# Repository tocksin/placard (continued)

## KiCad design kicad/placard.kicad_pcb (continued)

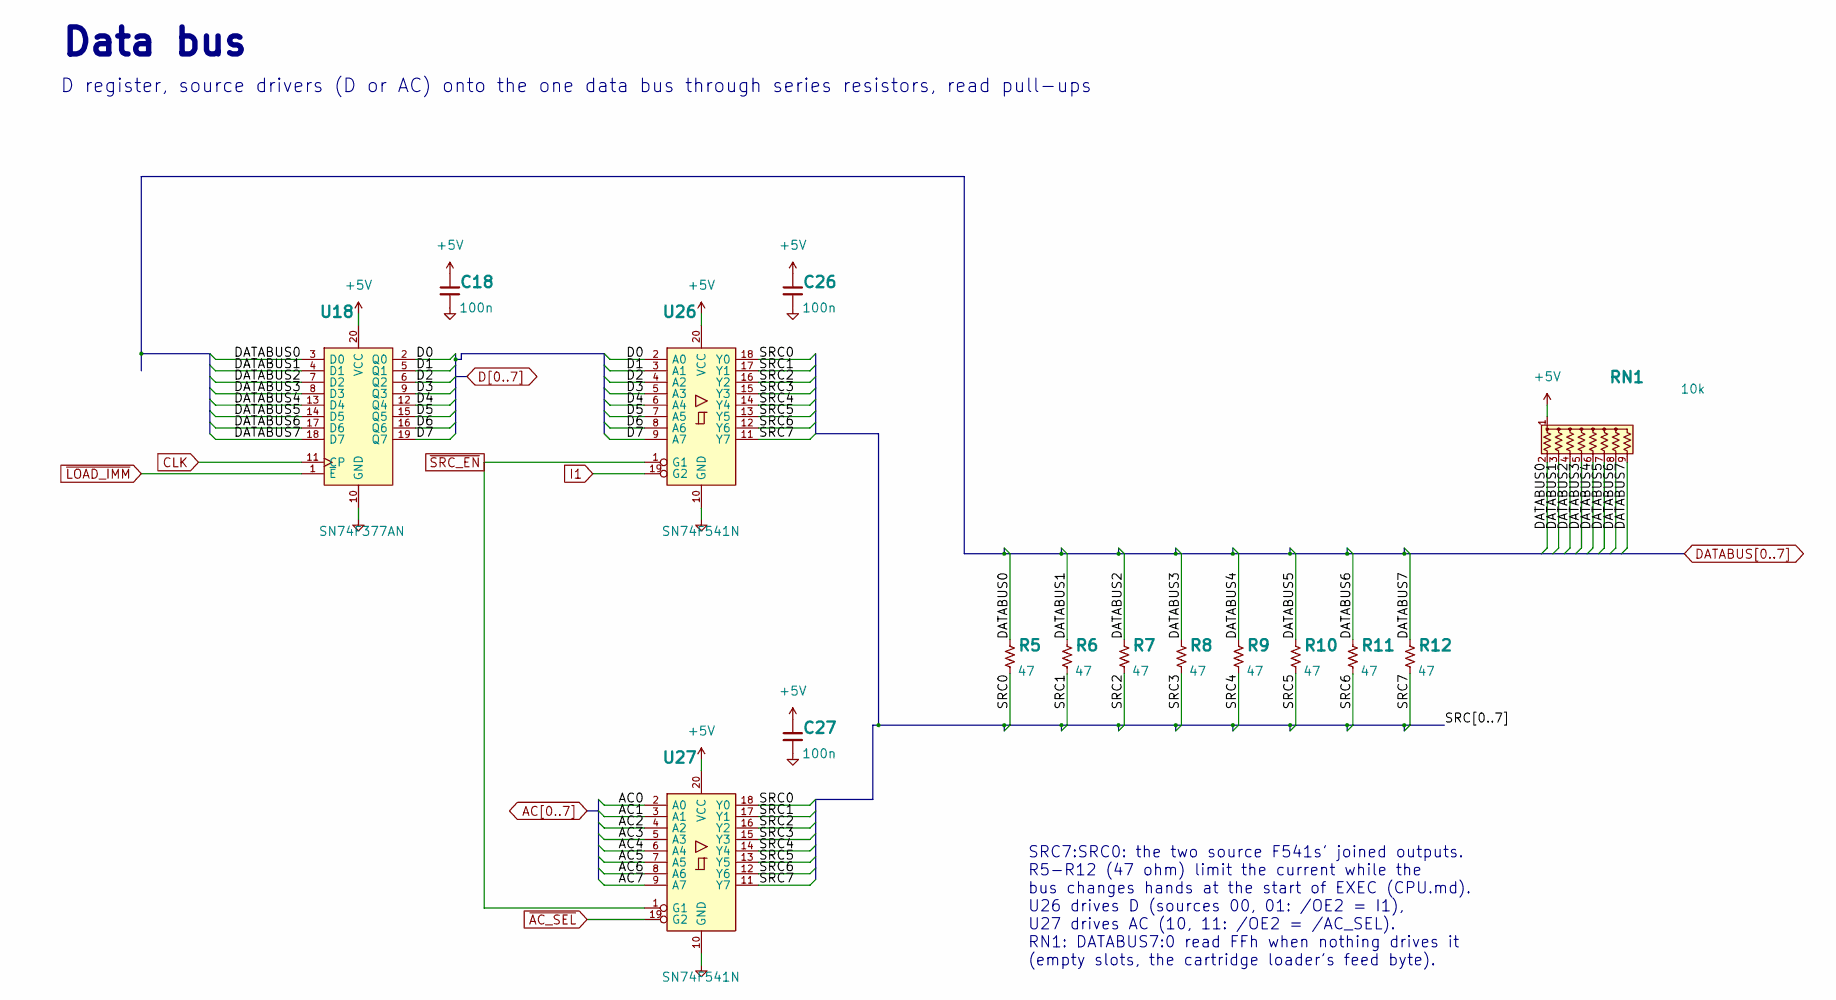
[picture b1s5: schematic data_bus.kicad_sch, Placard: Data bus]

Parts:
C18, C26, C27: 100n; C_Disc_D5.0mm_W2.5mm_P5.00mm; MPN FG28X7R1H104KNT00
R5, R6, R7, R8, R9, R10, R11, R12: 47; R_Axial_DIN0207_L6.3mm_D2.5mm_P10.16mm_Horizontal_Value; MPN MFR-25FBF52-47R
RN1: 10k; R_Array_SIP9; MPN 4609X-101-103LF
U18: SN74F377AN; DIP-20_W7.62mm_Socket_Puller; MPN SN74F377AN
U26, U27: SN74F541N; DIP-20_W7.62mm_Socket_Puller; MPN SN74F541N

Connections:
+5V: C18.1, C26.1, C27.1, RN1.1 (common), U18.20 (VCC), U26.20 (VCC), U27.20 (VCC); also elsewhere on the board
/Data bus/SRC0: R5.2, U26.18 (Y0), U27.18 (Y0)
/Data bus/SRC1: R6.2, U26.17 (Y1), U27.17 (Y1)
/Data bus/SRC2: R7.2, U26.16 (Y2), U27.16 (Y2)
/Data bus/SRC3: R8.2, U26.15 (Y3), U27.15 (Y3)
/Data bus/SRC4: R9.2, U26.14 (Y4), U27.14 (Y4)
/Data bus/SRC5: R10.2, U26.13 (Y5), U27.13 (Y5)
/Data bus/SRC6: R11.2, U26.12 (Y6), U27.12 (Y6)
/Data bus/SRC7: R12.2, U26.11 (Y7), U27.11 (Y7)
AC0: U27.2 (A0); also elsewhere on the board
AC1: U27.3 (A1); also elsewhere on the board
AC2: U27.4 (A2); also elsewhere on the board
AC3: U27.5 (A3); also elsewhere on the board
AC4: U27.6 (A4); also elsewhere on the board
AC5: U27.7 (A5); also elsewhere on the board
AC6: U27.8 (A6); also elsewhere on the board
AC7: U27.9 (A7); also elsewhere on the board
CLK: U18.11 (CP); also elsewhere on the board
D0: U18.2 (Q0), U26.2 (A0); also elsewhere on the board
D1: U18.5 (Q1), U26.3 (A1); also elsewhere on the board
D2: U18.6 (Q2), U26.4 (A2); also elsewhere on the board
D3: U18.9 (Q3), U26.5 (A3); also elsewhere on the board
D4: U18.12 (Q4), U26.6 (A4); also elsewhere on the board
D5: U18.15 (Q5), U26.7 (A5); also elsewhere on the board
D6: U18.16 (Q6), U26.8 (A6); also elsewhere on the board
D7: U18.19 (Q7), U26.9 (A7); also elsewhere on the board
DATABUS0: R5.1, RN1.2 (R1), U18.3 (D0); also elsewhere on the board
DATABUS1: R6.1, RN1.3 (R2), U18.4 (D1); also elsewhere on the board
DATABUS2: R7.1, RN1.4 (R3), U18.7 (D2); also elsewhere on the board
DATABUS3: R8.1, RN1.5 (R4), U18.8 (D3); also elsewhere on the board
DATABUS4: R9.1, RN1.6 (R5), U18.13 (D4); also elsewhere on the board
DATABUS5: R10.1, RN1.7 (R6), U18.14 (D5); also elsewhere on the board
DATABUS6: R11.1, RN1.8 (R7), U18.17 (D6); also elsewhere on the board
DATABUS7: R12.1, RN1.9 (R8), U18.18 (D7); also elsewhere on the board
GND: C18.2, C26.2, C27.2, U18.10 (GND), U26.10 (GND), U27.10 (GND); also elsewhere on the board
I1: U26.19 (G2); also elsewhere on the board
~AC_SEL: U27.19 (G2); also elsewhere on the board
~LOAD_IMM: U18.1 (~E); also elsewhere on the board
~SRC_EN: U26.1 (G1), U27.1 (G1); also elsewhere on the board

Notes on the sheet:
SRC7:SRC0: the two source F541s' joined outputs.
RN1: DATABUS7:0 read FFh when nothing drives it
U27 drives AC (10, 11: /OE2 = /AC_SEL).
R5-R12 (47 ohm) limit the current while the
Data bus
D register, source drivers (D or AC) onto the one data bus through series resistors, read pull-ups
bus changes hands at the start of EXEC (CPU.md).
U26 drives D (sources 00, 01: /OE2 = I1),
(empty slots, the cartridge loader's feed byte).

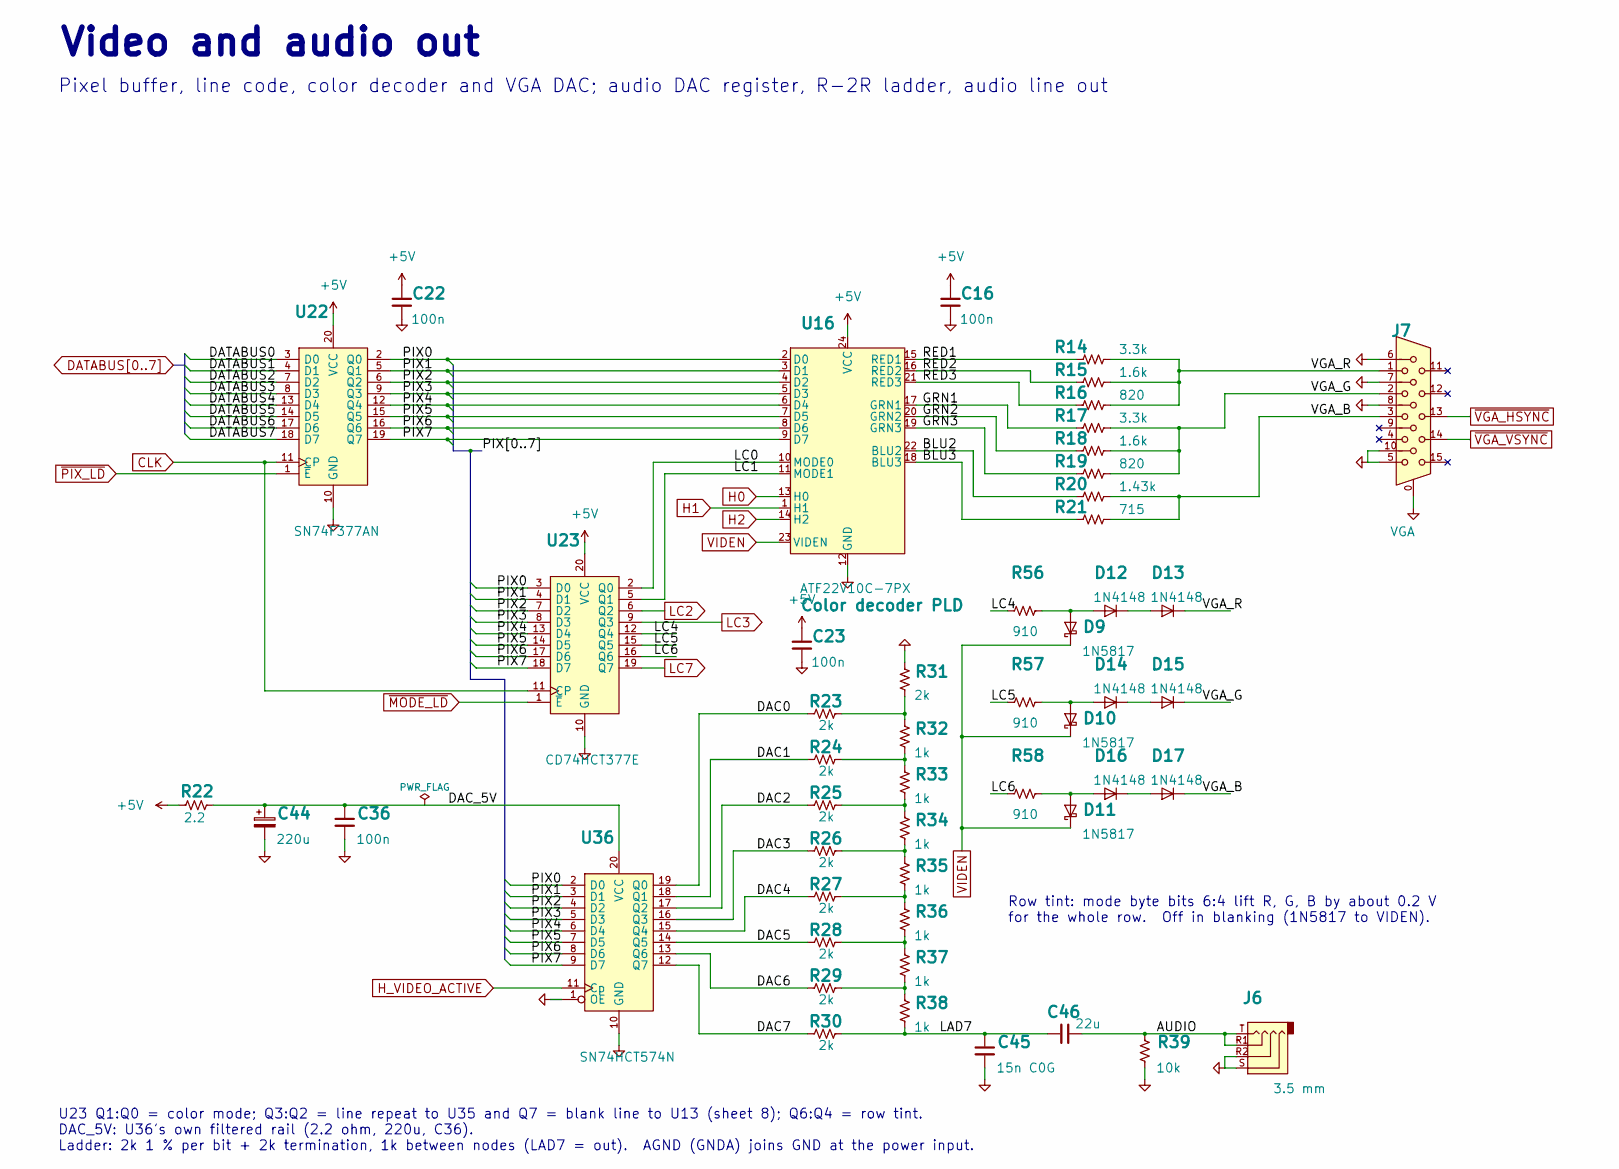
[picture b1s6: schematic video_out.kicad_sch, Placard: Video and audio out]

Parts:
C16, C22, C23, C36: 100n; C_Disc_D5.0mm_W2.5mm_P5.00mm; MPN FG28X7R1H104KNT00
C44: 220u; CP_Radial_D6.3mm_P2.50mm; MPN 25YXJ220M6.3X11
C45: 15n C0G; C_Disc_D5.0mm_W2.5mm_P5.00mm; MPN FG24C0G1H153JNT06
C46: 22u; C_Disc_D5.0mm_W2.5mm_P5.00mm; MPN FG22X7R1E226MRT06
D9, D10, D11: 1N5817; D_DO-41_SOD81_P7.62mm_Horizontal_Pad1.6; MPN 1N5817-TP
D12, D13, D14, D15, D16, D17: 1N4148; D_DO-35_SOD27_P7.62mm_Horizontal; MPN 1N4148-TAP
J6: 3.5 mm; Jack_3.5mm_Tensility_54-00174_Horizontal; MPN 54-00174
J7: VGA; DSUB-15-HD_Female_Horizontal_P2.29x1.98mm_EdgePinOffset3.03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; MPN A-HDF 15 A-KG/T
R14, R17: 3.3k; R_Axial_DIN0207_L6.3mm_D2.5mm_P10.16mm_Horizontal_Value; MPN MFR-25FBF52-3K3
R15, R18: 1.6k; R_Axial_DIN0207_L6.3mm_D2.5mm_P10.16mm_Horizontal_Value; MPN MFR-25FBF52-1K6
R16, R19: 820; R_Axial_DIN0207_L6.3mm_D2.5mm_P10.16mm_Horizontal_Value; MPN MFR-25FBF52-820R
R20: 1.43k; R_Axial_DIN0207_L6.3mm_D2.5mm_P10.16mm_Horizontal_Value; MPN MFR-25FBF52-1K43
R21: 715; R_Axial_DIN0207_L6.3mm_D2.5mm_P10.16mm_Horizontal_Value; MPN MFR-25FBF52-715R
R22: 2.2; R_Axial_DIN0207_L6.3mm_D2.5mm_P10.16mm_Horizontal_Value; MPN MFR-25FBF52-2R2
R23, R24, R25, R26, R27, R28, R29, R30, R31: 2k; R_Axial_DIN0207_L6.3mm_D2.5mm_P10.16mm_Horizontal_Value; MPN MFR-25FBF52-2K
R32, R33, R34, R35, R36, R37, R38: 1k; R_Axial_DIN0207_L6.3mm_D2.5mm_P10.16mm_Horizontal_Value; MPN MFR-25FBF52-1K
R39: 10k; R_Axial_DIN0207_L6.3mm_D2.5mm_P10.16mm_Horizontal_Value; MPN MFR-25FBF52-10K
R56, R57, R58: 910; R_Axial_DIN0207_L6.3mm_D2.5mm_P10.16mm_Horizontal_Value; MPN MFR-25FBF52-910R
U16: ATF22V10C-7PX; DIP-24_W7.62mm_Socket_Puller; MPN ATF22V10C-7PX
U22: SN74F377AN; DIP-20_W7.62mm_Socket_Puller; MPN SN74F377AN
U23: CD74HCT377E; DIP-20_W7.62mm_Socket_Puller; MPN CD74HCT377E
U36: SN74HCT574N; DIP-20_W7.62mm_Socket_Puller; MPN SN74HCT574N

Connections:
+5V: C16.1, C22.1, C23.1, R22.1, U16.24 (VCC), U22.20 (VCC), U23.20 (VCC); also elsewhere on the board
/Video and audio out/AUDIO: C46.2, J6.R1, J6.T, R39.1
/Video and audio out/BLU2: R20.1, U16.22 (BLU2)
/Video and audio out/BLU3: R21.1, U16.18 (BLU3)
/Video and audio out/DAC0: R23.1, U36.19 (Q0)
/Video and audio out/DAC1: R24.1, U36.18 (Q1)
/Video and audio out/DAC2: R25.1, U36.17 (Q2)
/Video and audio out/DAC3: R26.1, U36.16 (Q3)
/Video and audio out/DAC4: R27.1, U36.15 (Q4)
/Video and audio out/DAC5: R28.1, U36.14 (Q5)
/Video and audio out/DAC6: R29.1, U36.13 (Q6)
/Video and audio out/DAC7: R30.1, U36.12 (Q7)
/Video and audio out/DAC_5V: C36.1, C44.1, R22.2, U36.20 (VCC)
/Video and audio out/GRN1: R17.1, U16.17 (GRN1)
/Video and audio out/GRN2: R18.1, U16.20 (GRN2)
/Video and audio out/GRN3: R19.1, U16.19 (GRN3)
/Video and audio out/LAD7: C45.1, C46.1, R30.2, R38.2
/Video and audio out/LC0: U16.10 (MODE0), U23.2 (Q0)
/Video and audio out/LC1: U16.11 (MODE1), U23.5 (Q1)
/Video and audio out/LC4: R56.1, U23.12 (Q4)
/Video and audio out/LC5: R57.1, U23.15 (Q5)
/Video and audio out/LC6: R58.1, U23.16 (Q6)
/Video and audio out/PIX0: U16.2 (D0), U22.2 (Q0), U23.3 (D0), U36.2 (D0)
/Video and audio out/PIX1: U16.3 (D1), U22.5 (Q1), U23.4 (D1), U36.3 (D1)
/Video and audio out/PIX2: U16.4 (D2), U22.6 (Q2), U23.7 (D2), U36.4 (D2)
/Video and audio out/PIX3: U16.5 (D3), U22.9 (Q3), U23.8 (D3), U36.5 (D3)
/Video and audio out/PIX4: U16.6 (D4), U22.12 (Q4), U23.13 (D4), U36.6 (D4)
/Video and audio out/PIX5: U16.7 (D5), U22.15 (Q5), U23.14 (D5), U36.7 (D5)
/Video and audio out/PIX6: U16.8 (D6), U22.16 (Q6), U23.17 (D6), U36.8 (D6)
/Video and audio out/PIX7: U16.9 (D7), U22.19 (Q7), U23.18 (D7), U36.9 (D7)
/Video and audio out/RED1: R14.1, U16.15 (RED1)
/Video and audio out/RED2: R15.1, U16.16 (RED2)
/Video and audio out/RED3: R16.1, U16.21 (RED3)
/Video and audio out/VGA_B: D17.1 (K), J7.3, R20.2, R21.2
/Video and audio out/VGA_G: D15.1 (K), J7.2, R17.2, R18.2, R19.2
/Video and audio out/VGA_R: D13.1 (K), J7.1, R14.2, R15.2, R16.2
CLK: U22.11 (CP), U23.11 (CP); also elsewhere on the board
DATABUS0: U22.3 (D0); also elsewhere on the board
DATABUS1: U22.4 (D1); also elsewhere on the board
DATABUS2: U22.7 (D2); also elsewhere on the board
DATABUS3: U22.8 (D3); also elsewhere on the board
DATABUS4: U22.13 (D4); also elsewhere on the board
DATABUS5: U22.14 (D5); also elsewhere on the board
DATABUS6: U22.17 (D6); also elsewhere on the board
DATABUS7: U22.18 (D7); also elsewhere on the board
GND: C16.2, C22.2, C23.2, J7.0, J7.5, J7.6, J7.7, J7.8, J7.10, U16.12 (GND), U22.10 (GND), U23.10 (GND); also elsewhere on the board
GNDA: C36.2, C44.2, C45.2, J6.R2, J6.S, R31.1, R39.2, U36.1 (OE), U36.10 (GND); also elsewhere on the board
H0: U16.13 (H0); also elsewhere on the board
H1: U16.1 (H1); also elsewhere on the board
H2: U16.14 (H2); also elsewhere on the board
H_VIDEO_ACTIVE: U36.11 (Cp); also elsewhere on the board
LC2: U23.6 (Q2); also elsewhere on the board
LC3: U23.9 (Q3); also elsewhere on the board
LC7: U23.19 (Q7); also elsewhere on the board
unnamed: D10.2 (A), D14.2 (A), R57.2
unnamed: D11.2 (A), D16.2 (A), R58.2
unnamed: D9.2 (A), D12.2 (A), R56.2
unnamed: D12.1 (K), D13.2 (A)
unnamed: D14.1 (K), D15.2 (A)
unnamed: D16.1 (K), D17.2 (A)
unnamed: R23.2, R31.2, R32.1
unnamed: R24.2, R32.2, R33.1
unnamed: R25.2, R33.2, R34.1
unnamed: R26.2, R34.2, R35.1
unnamed: R27.2, R35.2, R36.1
unnamed: R28.2, R36.2, R37.1
unnamed: R29.2, R37.2, R38.1
VIDEN: D9.1 (K), D10.1 (K), D11.1 (K), U16.23 (VIDEN); also elsewhere on the board
~MODE_LD: U23.1 (~E); also elsewhere on the board
~PIX_LD: U22.1 (~E); also elsewhere on the board
~VGA_HSYNC: J7.13; also elsewhere on the board
~VGA_VSYNC: J7.14; also elsewhere on the board

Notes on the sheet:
Pixel buffer, line code, color decoder and VGA DAC; audio DAC register, R-2R ladder, audio line out
Video and audio out
U23 Q1:Q0 = color mode; Q3:Q2 = line repeat to U35 and Q7 = blank line to U13 (sheet 8); Q6:Q4 = row tint.
Row tint: mode byte bits 6:4 lift R, G, B by about 0.2 V
DAC_5V: U36's own filtered rail (2.2 ohm, 220u, C36).
for the whole row. Off in blanking (1N5817 to VIDEN).
Ladder: 2k 1 % per bit + 2k termination, 1k between nodes (LAD7 = out). AGND (GNDA) joins GND at the power input.

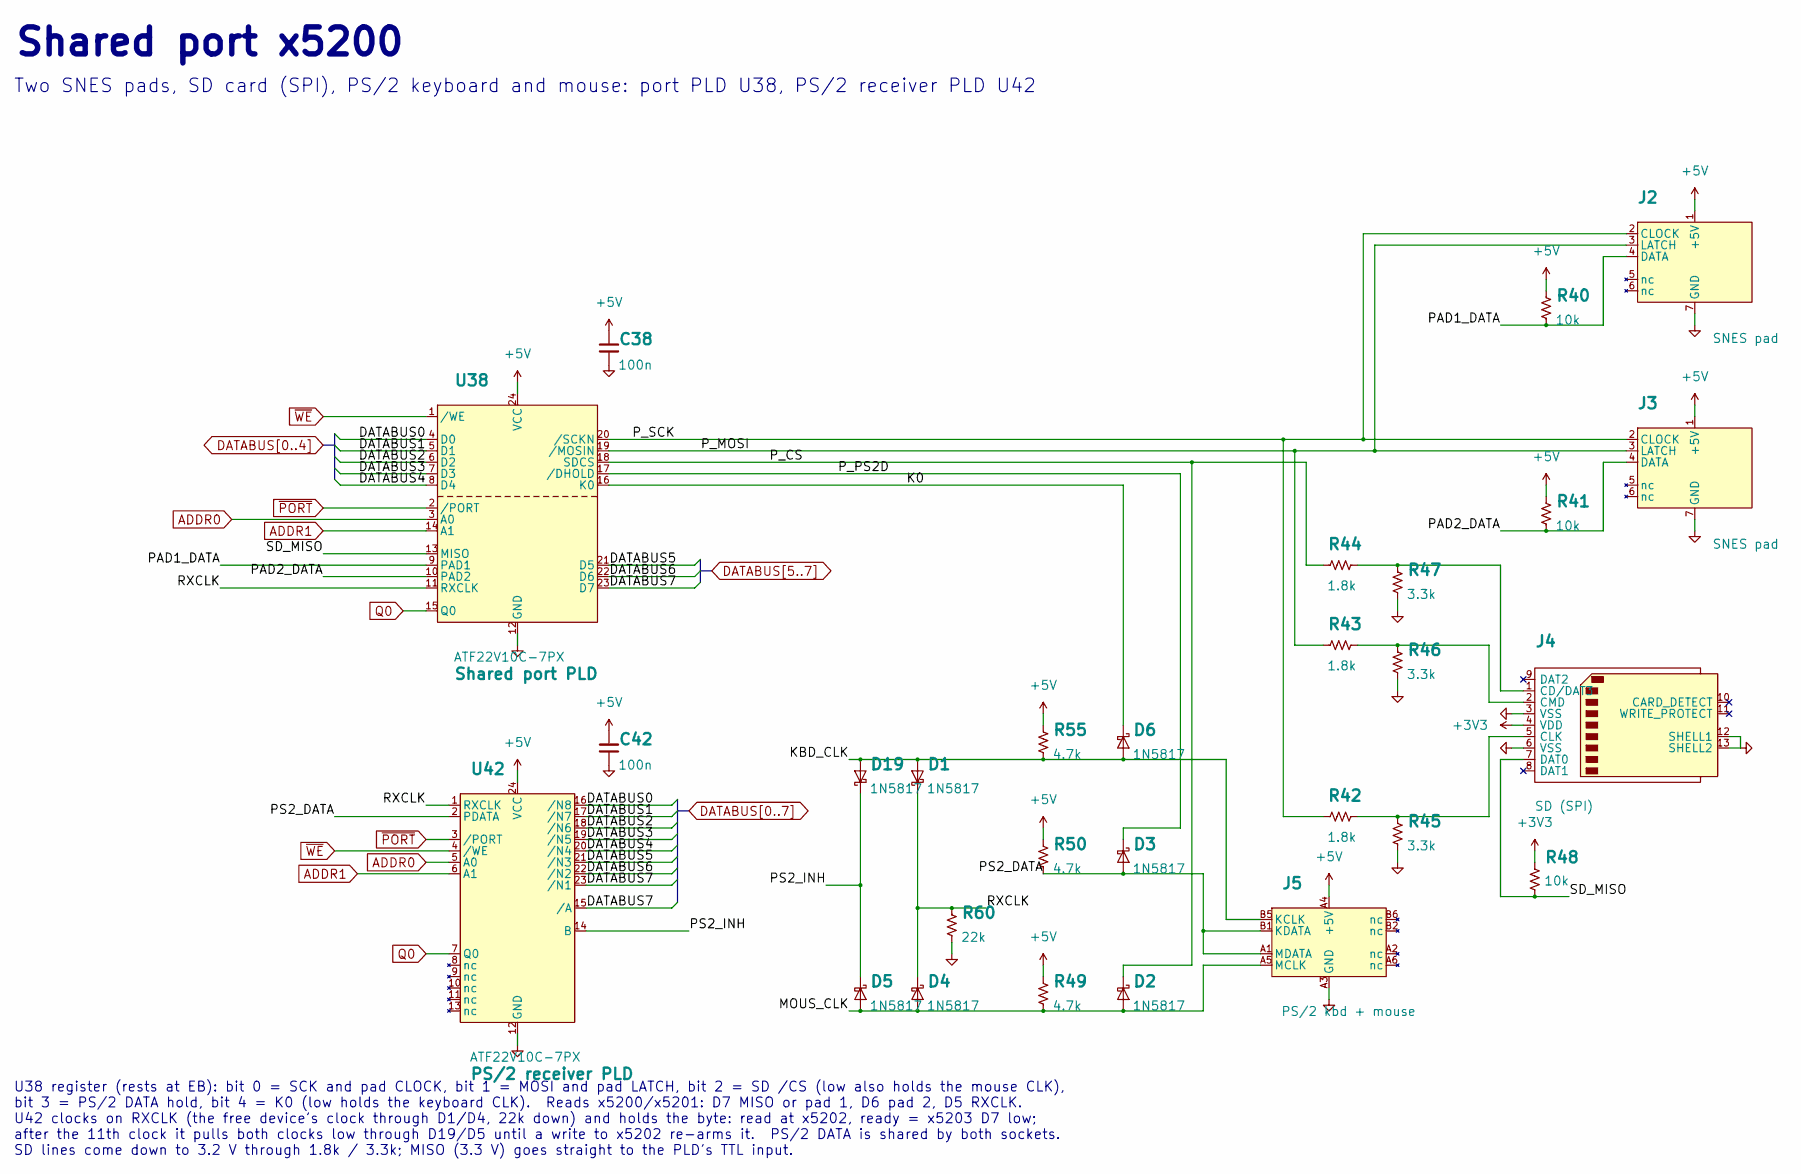
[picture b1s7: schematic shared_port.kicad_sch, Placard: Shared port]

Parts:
C38, C42: 100n; C_Disc_D5.0mm_W2.5mm_P5.00mm; MPN FG28X7R1H104KNT00
D1, D2, D3, D4, D5, D6, D19: 1N5817; D_DO-41_SOD81_P7.62mm_Horizontal_Pad1.6; MPN 1N5817-TP
J2, J3: SNES pad; SNES_Pad_Socket_Horizontal
J4: SD (SPI); SD_Hirose_DM1AA_SF_PEJ82; MPN DM1AA-SF-PEJ(82)
J5: PS/2 kbd + mouse; PS2_Kycon_KMDGX-6S-6S-S4N; MPN KMDGX-6S/6S-S4N
R40, R41, R48: 10k; R_Axial_DIN0207_L6.3mm_D2.5mm_P10.16mm_Horizontal_Value; MPN MFR-25FBF52-10K
R42, R43, R44: 1.8k; R_Axial_DIN0207_L6.3mm_D2.5mm_P10.16mm_Horizontal_Value; MPN MFR-25FBF52-1K8
R45, R46, R47: 3.3k; R_Axial_DIN0207_L6.3mm_D2.5mm_P10.16mm_Horizontal_Value; MPN MFR-25FBF52-3K3
R49, R50, R55: 4.7k; R_Axial_DIN0207_L6.3mm_D2.5mm_P10.16mm_Horizontal_Value; MPN MFR-25FBF52-4K7
R60: 22k; R_Axial_DIN0207_L6.3mm_D2.5mm_P10.16mm_Horizontal_Value; MPN MFR-25FBF52-22K
U38, U42: ATF22V10C-7PX; DIP-24_W7.62mm_Socket_Puller; MPN ATF22V10C-7PX

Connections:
+3V3: J4.4 (VDD), R48.1; also elsewhere on the board
+5V: C38.1, C42.1, J2.1 (+5V), J3.1 (+5V), J5.A4 (+5V), J5.B4 (+5V), R40.1, R41.1, R49.1, R50.1, R55.1, U38.24 (VCC), U42.24 (VCC); also elsewhere on the board
/Shared port/K0: D6.1 (K), U38.16 (K0)
/Shared port/KBD_CLK: D1.2 (A), D6.2 (A), D19.2 (A), J5.B5 (KCLK), R55.2
/Shared port/MOUS_CLK: D2.2 (A), D4.2 (A), D5.2 (A), J5.A5 (MCLK), R49.2
/Shared port/PAD1_DATA: J2.4 (DATA), R40.2, U38.9 (PAD1)
/Shared port/PAD2_DATA: J3.4 (DATA), R41.2, U38.10 (PAD2)
/Shared port/PS2_DATA: D3.2 (A), J5.A1 (MDATA), J5.B1 (KDATA), R50.2, U42.2 (PDATA)
/Shared port/PS2_INH: D5.1 (K), D19.1 (K), U42.14 (B)
/Shared port/P_CS: D2.1 (K), R44.1, U38.18 (SDCS)
/Shared port/P_MOSI: J2.3 (LATCH), J3.3 (LATCH), R43.1, U38.19 (/MOSIN)
/Shared port/P_PS2D: D3.1 (K), U38.17 (/DHOLD)
/Shared port/P_SCK: J2.2 (CLOCK), J3.2 (CLOCK), R42.1, U38.20 (/SCKN)
/Shared port/RXCLK: D1.1 (K), D4.1 (K), R60.1, U38.11 (RXCLK), U42.1 (RXCLK)
/Shared port/SD_MISO: J4.7 (DAT0), R48.2, U38.13 (MISO)
ADDR0: U38.3 (A0), U42.5 (A0); also elsewhere on the board
ADDR1: U38.14 (A1), U42.6 (A1); also elsewhere on the board
DATABUS0: U38.4 (D0), U42.16 (/N8); also elsewhere on the board
DATABUS1: U38.5 (D1), U42.17 (/N7); also elsewhere on the board
DATABUS2: U38.6 (D2), U42.18 (/N6); also elsewhere on the board
DATABUS3: U38.7 (D3), U42.19 (/N5); also elsewhere on the board
DATABUS4: U38.8 (D4), U42.20 (/N4); also elsewhere on the board
DATABUS5: U38.21 (D5), U42.21 (/N3); also elsewhere on the board
DATABUS6: U38.22 (D6), U42.22 (/N2); also elsewhere on the board
DATABUS7: U38.23 (D7), U42.15 (/A), U42.23 (/N1); also elsewhere on the board
GND: C38.2, C42.2, J2.7 (GND), J3.7 (GND), J4.3 (VSS), J4.6 (VSS), J4.12 (SHELL1), J4.13 (SHELL2), J5.A3 (GND), J5.B3 (GND), J5.SH (SHIELD), R45.2, R46.2, R47.2, R60.2, U38.12 (GND), U42.12 (GND); also elsewhere on the board
unnamed: J4.1 (CD/DAT3), R44.2, R47.1
unnamed: J4.5 (CLK), R42.2, R45.1
unnamed: J4.2 (CMD), R43.2, R46.1
Q0: U38.15 (nc), U42.7 (nc); also elsewhere on the board
~PORT: U38.2 (/PORT_RD), U42.3 (/PORT_RD); also elsewhere on the board
~WE: U38.1 (/PORT_WR), U42.4 (/PORT_WR); also elsewhere on the board

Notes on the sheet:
Shared port x5200
bit 3 = PS/2 DATA hold, bit 4 = K0 (low holds the keyboard CLK). Reads x5200/x5201: D7 MISO or pad 1, D6 pad 2, D5 RXCLK.
U38 register (rests at EB): bit 0 = SCK and pad CLOCK, bit 1 = MOSI and pad LATCH, bit 2 = SD /CS (low also holds the mouse CLK),
SD lines come down to 3.2 V through 1.8k / 3.3k; MISO (3.3 V) goes straight to the PLD's TTL input.
Two SNES pads, SD card (SPI), PS/2 keyboard and mouse: port PLD U38, PS/2 receiver PLD U42
after the 11th clock it pulls both clocks low through D19/D5 until a write to x5202 re-arms it. PS/2 DATA is shared by both sockets.
U42 clocks on RXCLK (the free device's clock through D1/D4, 22k down) and holds the byte: read at x5202, ready = x5203 D7 low;

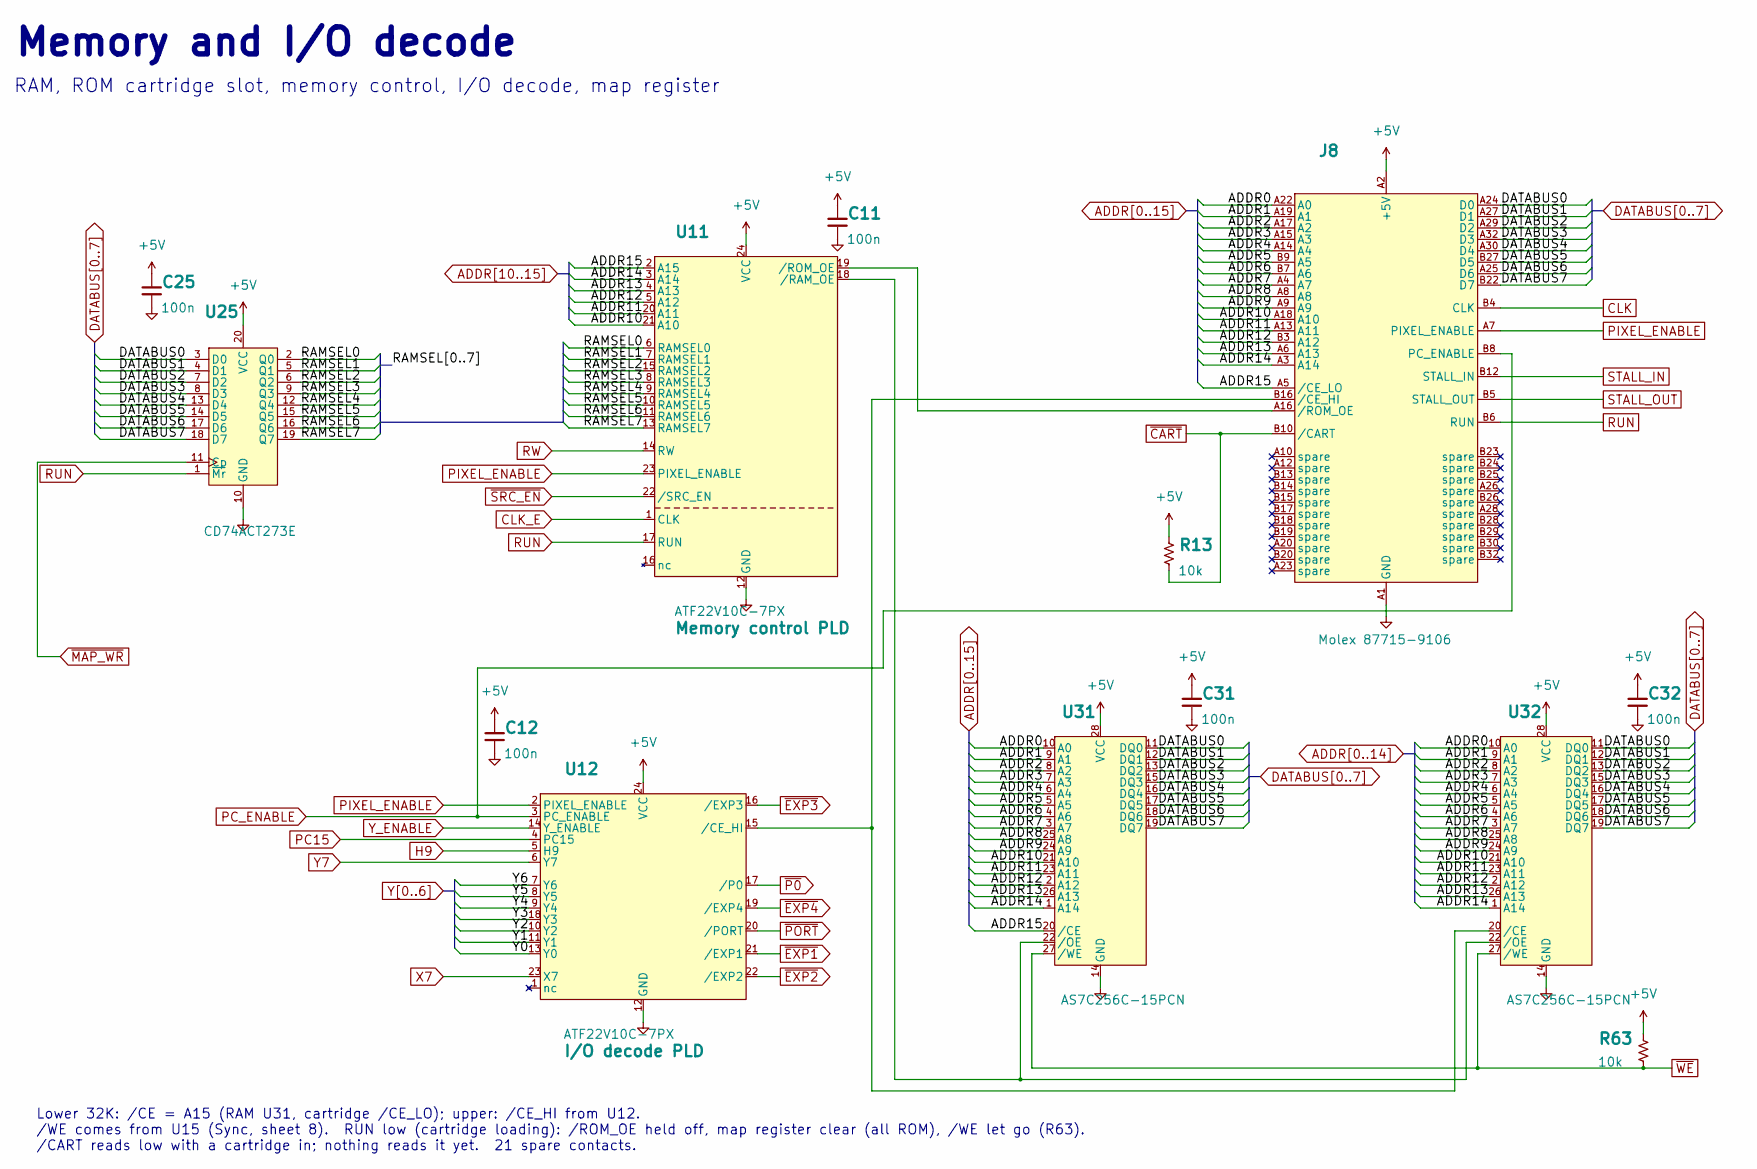
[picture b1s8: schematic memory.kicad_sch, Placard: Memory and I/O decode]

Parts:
C11, C12, C25, C31, C32: 100n; C_Disc_D5.0mm_W2.5mm_P5.00mm; MPN FG28X7R1H104KNT00
J8: Molex 87715-9106; Molex_87715-9106_PCIe_x4_Vertical; MPN 87715-9106
R13, R63: 10k; R_Axial_DIN0207_L6.3mm_D2.5mm_P10.16mm_Horizontal_Value; MPN MFR-25FBF52-10K
U11, U12: ATF22V10C-7PX; DIP-24_W7.62mm_Socket_Puller; MPN ATF22V10C-7PX
U25: CD74ACT273E; DIP-20_W7.62mm_Socket_Puller; MPN CD74ACT273E
U31, U32: AS7C256C-15PCN; DIP-28_W7.62mm_Socket_Puller; MPN AS7C256C-15PCN

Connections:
+5V: C11.1, C12.1, C25.1, C31.1, C32.1, J8.A2 (+5V), J8.B2 (+5V), R13.1, R63.1, U11.24 (VCC), U12.24 (VCC), U25.20 (VCC), U31.28 (VCC), U32.28 (VCC); also elsewhere on the board
/Memory and I/O decode/RAMSEL0: U11.6 (RAMSEL0), U25.2 (Q0)
/Memory and I/O decode/RAMSEL1: U11.7 (RAMSEL1), U25.5 (Q1)
/Memory and I/O decode/RAMSEL2: U11.15 (RAMSEL2), U25.6 (Q2)
/Memory and I/O decode/RAMSEL3: U11.8 (RAMSEL3), U25.9 (Q3)
/Memory and I/O decode/RAMSEL4: U11.9 (RAMSEL4), U25.12 (Q4)
/Memory and I/O decode/RAMSEL5: U11.10 (RAMSEL5), U25.15 (Q5)
/Memory and I/O decode/RAMSEL6: U11.11 (RAMSEL6), U25.16 (Q6)
/Memory and I/O decode/RAMSEL7: U11.13 (RAMSEL7), U25.19 (Q7)
ADDR0: J8.A22 (A0), U31.10 (A0), U32.10 (A0); also elsewhere on the board
ADDR1: J8.A19 (A1), U31.9 (A1), U32.9 (A1); also elsewhere on the board
ADDR2: J8.A17 (A2), U31.8 (A2), U32.8 (A2); also elsewhere on the board
ADDR3: J8.A15 (A3), U31.7 (A3), U32.7 (A3); also elsewhere on the board
ADDR4: J8.A14 (A4), U31.6 (A4), U32.6 (A4); also elsewhere on the board
ADDR5: J8.B9 (A5), U31.5 (A5), U32.5 (A5); also elsewhere on the board
ADDR6: J8.B7 (A6), U31.4 (A6), U32.4 (A6); also elsewhere on the board
ADDR7: J8.A4 (A7), U31.3 (A7), U32.3 (A7); also elsewhere on the board
ADDR8: J8.A8, U31.25 (A8), U32.25 (A8); also elsewhere on the board
ADDR9: J8.A9, U31.24 (A9), U32.24 (A9); also elsewhere on the board
ADDR10: J8.A18 (A10), U11.21 (A10), U31.21 (A10), U32.21 (A10); also elsewhere on the board
ADDR11: J8.A13 (A11), U11.20 (A11), U31.23 (A11), U32.23 (A11); also elsewhere on the board
ADDR12: J8.B3 (A12), U11.5 (A12), U31.2 (A12), U32.2 (A12); also elsewhere on the board
ADDR13: J8.A6 (A13), U11.4 (A13), U31.26 (A13), U32.26 (A13); also elsewhere on the board
ADDR14: J8.A3 (A14), U11.3 (A14), U31.1 (A14), U32.1 (A14); also elsewhere on the board
ADDR15: J8.A5 (/CE_LO), U11.2 (A15), U31.20 (/CE); also elsewhere on the board
CLK: J8.B4 (CLK); also elsewhere on the board
CLK_E: U11.1 (CLK); also elsewhere on the board
DATABUS0: J8.A24 (D0), U25.3 (D0), U31.11 (DQ0), U32.11 (DQ0); also elsewhere on the board
DATABUS1: J8.A27 (D1), U25.4 (D1), U31.12 (DQ1), U32.12 (DQ1); also elsewhere on the board
DATABUS2: J8.A29 (D2), U25.7 (D2), U31.13 (DQ2), U32.13 (DQ2); also elsewhere on the board
DATABUS3: J8.A32 (D3), U25.8 (D3), U31.15 (DQ3), U32.15 (DQ3); also elsewhere on the board
DATABUS4: J8.A30 (D4), U25.13 (D4), U31.16 (DQ4), U32.16 (DQ4); also elsewhere on the board
DATABUS5: J8.B27 (D5), U25.14 (D5), U31.17 (DQ5), U32.17 (DQ5); also elsewhere on the board
DATABUS6: J8.A25 (D6), U25.17 (D6), U31.18 (DQ6), U32.18 (DQ6); also elsewhere on the board
DATABUS7: J8.B22 (D7), U25.18 (D7), U31.19 (DQ7), U32.19 (DQ7); also elsewhere on the board
GND: C11.2, C12.2, C25.2, C31.2, C32.2, J8.A1 (GND), J8.A11 (GND), J8.A21 (GND), J8.A31 (GND), J8.B1 (GND), J8.B11 (GND), J8.B21 (GND), J8.B31 (GND), U11.12 (GND), U12.12 (GND), U25.10 (GND), U31.14 (GND), U32.14 (GND); also elsewhere on the board
H9: U12.5 (H9); also elsewhere on the board
unnamed: J8.B16 (/CE_HI), U12.15 (/CE_HI), U32.20 (/CE)
unnamed: J8.A16 (/ROM_OE), U11.19 (/ROM_OE)
unnamed: U11.18 (/RAM_OE), U31.22 (/OE), U32.22 (/OE)
PC15: U12.4 (PC15); also elsewhere on the board
PC_ENABLE: J8.B8 (PC_ENABLE), U12.3 (PC_ENABLE); also elsewhere on the board
PIXEL_ENABLE: J8.A7 (PIXEL_ENABLE), U11.23 (PIXEL_ENABLE), U12.2 (PIXEL_ENABLE); also elsewhere on the board
RUN: J8.B6 (RUN), U11.17 (RUN), U25.1 (~Mr); also elsewhere on the board
RW: U11.14 (RW); also elsewhere on the board
STALL_IN: J8.B12 (STALL_IN); also elsewhere on the board
STALL_OUT: J8.B5 (STALL_OUT); also elsewhere on the board
X7: U12.23 (Q0); also elsewhere on the board
Y0: U12.13 (A8); also elsewhere on the board
Y1: U12.11 (A9); also elsewhere on the board
Y2: U12.10 (A10); also elsewhere on the board
Y3: U12.18 (A11); also elsewhere on the board
Y4: U12.9 (A12); also elsewhere on the board
Y5: U12.8 (A13); also elsewhere on the board
Y6: U12.7 (A14); also elsewhere on the board
Y7: U12.6 (Y7); also elsewhere on the board
Y_ENABLE: U12.14 (Y_ENABLE); also elsewhere on the board
~CART: J8.B10 (/CART), R13.2; also elsewhere on the board
~EXP1: U12.21 (/EXP1); also elsewhere on the board
~EXP2: U12.22 (/EXP2); also elsewhere on the board
~EXP3: U12.16 (/MAP_WR); also elsewhere on the board
~EXP4: U12.19 (/PORT_WR); also elsewhere on the board
~MAP_WR: U25.11 (Cp); also elsewhere on the board
~P0: U12.17 (/LINE_RD); also elsewhere on the board
~PORT: U12.20 (/PORT_RD); also elsewhere on the board
~SRC_EN: U11.22 (/SRC_EN); also elsewhere on the board
~WE: R63.2, U31.27 (/WE), U32.27 (/WE); also elsewhere on the board

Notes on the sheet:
/CART reads low with a cartridge in; nothing reads it yet. 21 spare contacts.
/WE comes from U15 (Sync, sheet 8). RUN low (cartridge loading): /ROM_OE held off, map register clear (all ROM), /WE let go (R63).
RAM, ROM cartridge slot, memory control, I/O decode, map register
Lower 32K: /CE = A15 (RAM U31, cartridge /CE_LO); upper: /CE_HI from U12.
Memory and I/O decode

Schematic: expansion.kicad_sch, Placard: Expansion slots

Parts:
J9: Slot 1; Molex_87715-9106_Expansion_Slot; MPN 87715-9106
J10: Slot 2; Molex_87715-9106_Expansion_Slot; MPN 87715-9106
J11: Slot 3; Molex_87715-9106_Expansion_Slot; MPN 87715-9106
J12: Slot 4; Molex_87715-9106_Expansion_Slot; MPN 87715-9106

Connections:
+5V: J9.A2 (+5V), J9.B2 (+5V), J10.A2 (+5V), J10.B2 (+5V), J11.A2 (+5V), J11.B2 (+5V), J12.A2 (+5V), J12.B2 (+5V); also elsewhere on the board
ADDR0: J9.A22 (A0), J10.A22 (A0), J11.A22 (A0), J12.A22 (A0); also elsewhere on the board
ADDR1: J9.A19 (A1), J10.A19 (A1), J11.A19 (A1), J12.A19 (A1); also elsewhere on the board
ADDR2: J9.A17 (A2), J10.A17 (A2), J11.A17 (A2), J12.A17 (A2); also elsewhere on the board
ADDR3: J9.A15 (A3), J10.A15 (A3), J11.A15 (A3), J12.A15 (A3); also elsewhere on the board
ADDR4: J9.A14 (A4), J10.A14 (A4), J11.A14 (A4), J12.A14 (A4); also elsewhere on the board
ADDR5: J9.B9 (A5), J10.B9 (A5), J11.B9 (A5), J12.B9 (A5); also elsewhere on the board
ADDR6: J9.B7 (A6), J10.B7 (A6), J11.B7 (A6), J12.B7 (A6); also elsewhere on the board
ADDR7: J9.A4 (A7), J10.A4 (A7), J11.A4 (A7), J12.A4 (A7); also elsewhere on the board
ADDR8: J9.A8, J10.A8, J11.A8, J12.A8; also elsewhere on the board
ADDR9: J9.A9, J10.A9, J11.A9, J12.A9; also elsewhere on the board
ADDR10: J9.A18 (A10), J10.A18 (A10), J11.A18 (A10), J12.A18 (A10); also elsewhere on the board
ADDR11: J9.A13 (A11), J10.A13 (A11), J11.A13 (A11), J12.A13 (A11); also elsewhere on the board
ADDR12: J9.B3 (A12), J10.B3 (A12), J11.B3 (A12), J12.B3 (A12); also elsewhere on the board
ADDR13: J9.A6 (A13), J10.A6 (A13), J11.A6 (A13), J12.A6 (A13); also elsewhere on the board
ADDR14: J9.A3 (A14), J10.A3 (A14), J11.A3 (A14), J12.A3 (A14); also elsewhere on the board
ADDR15: J9.A5 (A15), J10.A5 (A15), J11.A5 (A15), J12.A5 (A15); also elsewhere on the board
CLK: J9.B4 (CLK), J10.B4 (CLK), J11.B4 (CLK), J12.B4 (CLK); also elsewhere on the board
DATABUS0: J9.A23 (D0), J10.A23 (D0), J11.A23 (D0), J12.A23 (D0); also elsewhere on the board
DATABUS1: J9.B13 (D1), J10.B13 (D1), J11.B13 (D1), J12.B13 (D1); also elsewhere on the board
DATABUS2: J9.B15 (D2), J10.B15 (D2), J11.B15 (D2), J12.B15 (D2); also elsewhere on the board
DATABUS3: J9.B17 (D3), J10.B17 (D3), J11.B17 (D3), J12.B17 (D3); also elsewhere on the board
DATABUS4: J9.B19 (D4), J10.B19 (D4), J11.B19 (D4), J12.B19 (D4); also elsewhere on the board
DATABUS5: J9.B23 (D5), J10.B23 (D5), J11.B23 (D5), J12.B23 (D5); also elsewhere on the board
DATABUS6: J9.B25 (D6), J10.B25 (D6), J11.B25 (D6), J12.B25 (D6); also elsewhere on the board
DATABUS7: J9.B29 (D7), J10.B29 (D7), J11.B29 (D7), J12.B29 (D7); also elsewhere on the board
GND: J9.A1 (GND), J9.A11 (GND), J9.A12 (GND), J9.A21 (GND), J9.A31 (GND), J9.B1 (GND), J9.B11 (GND), J9.B18 (GND), J9.B21 (GND), J9.B26 (GND), J9.B30 (GND), J9.B31 (GND), J9.B32 (GND), J10.A1 (GND), J10.A11 (GND), J10.A12 (GND), J10.A21 (GND), J10.A31 (GND), J10.B1 (GND), J10.B11 (GND), J10.B18 (GND), J10.B21 (GND), J10.B26 (GND), J10.B30 (GND), J10.B31 (GND), J10.B32 (GND), J11.A1 (GND), J11.A11 (GND), J11.A12 (GND), J11.A21 (GND), J11.A31 (GND), J11.B1 (GND), J11.B11 (GND), J11.B18 (GND), J11.B21 (GND), J11.B26 (GND), J11.B30 (GND), J11.B31 (GND), J11.B32 (GND), J12.A1 (GND), J12.A11 (GND), J12.A12 (GND), J12.A21 (GND), J12.A31 (GND), J12.B1 (GND), J12.B11 (GND), J12.B18 (GND), J12.B21 (GND), J12.B26 (GND), J12.B30 (GND), J12.B31 (GND), J12.B32 (GND); also elsewhere on the board
PC_ENABLE: J9.B8 (BT3); also elsewhere on the board
PIXEL_ENABLE: J9.A7 (PIXEL_ENABLE), J10.A7 (PIXEL_ENABLE), J11.A7 (PIXEL_ENABLE), J12.A7 (PIXEL_ENABLE); also elsewhere on the board
Q0: J9.A10 (SEL), J10.A10 (SEL), J11.A10 (SEL), J12.A10 (SEL); also elsewhere on the board
RUN: J9.B20 (/RESET), J10.B20 (/RESET), J11.B20 (/RESET), J12.B20 (/RESET); also elsewhere on the board
RW: J9.B16 (RW), J10.B16 (RW), J11.B16 (RW), J12.B16 (RW); also elsewhere on the board
STALL_IN: J9.B12 (BT1); also elsewhere on the board
STALL_OUT: J9.B14 (BT2); also elsewhere on the board
~CART: J9.B28 (BT5); also elsewhere on the board
~EXP1: J9.A16 (/EXP); also elsewhere on the board
~EXP2: J10.A16 (/EXP); also elsewhere on the board
~EXP3: J11.A16 (/EXP); also elsewhere on the board
~EXP4: J12.A16 (/EXP); also elsewhere on the board
~HSYNC: J9.A26 (/HSYNC), J10.A26 (/HSYNC), J11.A26 (/HSYNC), J12.A26 (/HSYNC); also elsewhere on the board
~LOAD_IMM: J9.A20 (LOAD_IMM), J10.A20 (LOAD_IMM), J11.A20 (LOAD_IMM), J12.A20 (LOAD_IMM); also elsewhere on the board
~VSYNC: J9.A28 (/VSYNC), J10.A28 (/VSYNC), J11.A28 (/VSYNC), J12.A28 (/VSYNC); also elsewhere on the board
~WE: J9.B24 (/WE), J10.B24 (/WE), J11.B24 (/WE), J12.B24 (/WE); also elsewhere on the board

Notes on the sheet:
Expansion slots
Four slots (Molex 87715-9106, as the cartridge), x5100-x53FF, 128 bytes each (EXPANSION.md)
A10 = Q0 (State PLD, 0 in LOAD_MEM): a plain SRAM card takes /CE = /EXPn, /OE = Q0, /WE = /WE.
Each slot has its own select: /EXP1-/EXP4 (I/O decode PLD rev 07). /RESET = RUN (low while the cartridge loads).
BT1, BT2, BT3, BT5 (boot contacts): slot 1 only, STALL_IN, STALL_OUT, PC_ENABLE, /CART; cards latch DATABUS7:0.
LOAD_IMM carries the State PLD's /LOAD_IMM (low when the CPU latches the read bus into D).
Molex 87715-9106 since 2026-10-30: ADDR15:0, PIXEL_ENABLE, /HSYNC, /VSYNC on every slot (cards can follow the video);
the contacts a cartridge drives are left open, so a cartridge in the wrong slot is harmless.
